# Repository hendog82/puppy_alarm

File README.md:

# Puppy Alarm Clock
Do you hate waking up to your alarm clock? Well, now you can wake up to your puppy licking your face instead. 

This gadget allows you to set a wake up time, and then it will open your dogs crate at the specified time, allowing your dog to jump on your bed and wake you up. 

### Firmware
The firmware is based on the [restful server example](https://github.com/espressif/esp-idf/tree/master/examples/protocols/http_server/restful_server) from the ESP-IDF. The firmware connects to the WiFi network and hosts a local website (so that any device connected to the same network can access it).

Users can connect to this local web page to set the alarm time (using post requests). The ESP gets the current time using NTP, and if the times match the ESP will turn on the motor, opening the dog create. 

### Webpage
The webpage has a live clock and selectable options to set the wake up time, which is then sent to the ESP 32 using a post request. The source code is in the `/front/web-demo/dist` folder.

### Hardware
I generated a simple 2-layer PCB using EAGLE. The files are in the `/board_files` folder. This PCB connects the [ESP-32 huzzah Dev board](https://www.adafruit.com/product/3405) to an H-Bridge that can drive the motor in either direction, and to a button that is used to reset the motor position (or any other desired function. It also has LED's to indicate motor spin direction. The board is powered using 5V from the micro-usb port on the dev board.

#### Pin Assignment:
The following GPIO's of the ESP32 Dev Board are connected

| ESP32  | Function       |
| ------ | -------        |
| GPIO27 | Motor Forwards |
| GPIO33 | Motor Backwards|
| GPIO16 | Button Input   |

### 3D Printed Housing
The STL files for the 3D printed housing are in the `/housing` folder.

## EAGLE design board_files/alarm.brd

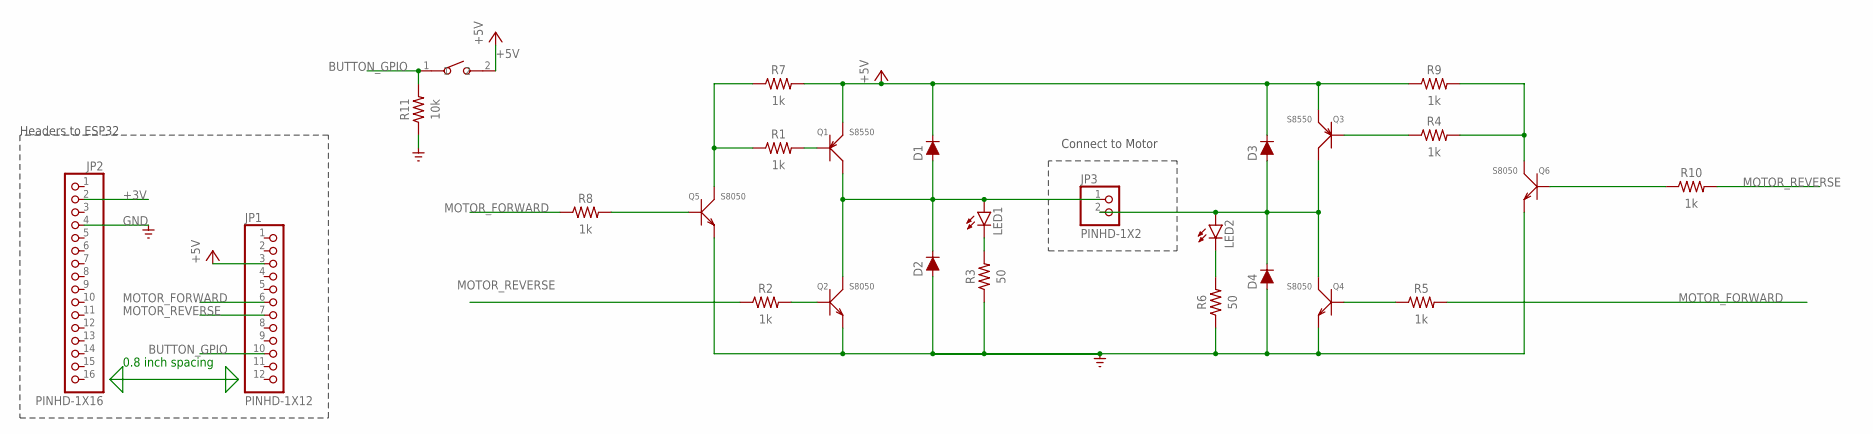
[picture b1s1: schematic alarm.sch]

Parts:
D1, D2, D3, D4: 250mA/100V; SOD-323
JP1: PINHD-1X12; 1X12
JP2: PINHD-1X16; 1X16
JP3: PINHD-1X2; 1X02
LED1: LED-GREEN0603; 0603-GREEN
LED2: LED-ORANGE0603; 0603-ORANGE
Q1, Q3: S8550; SOT-23
Q2, Q4, Q5, Q6: S8050; SOT-23
R1, R2, R4, R5, R7, R8, R9, R10: 1k; RESC1608X60
R3, R6: 50; RESC1608X60
R11: 10k; RESC1608X60
SW1: B3U-1000P-2P-SMD; SW2-2.6-3.0X2.5X1.2+0.4MM

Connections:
+3V: JP2.2
+5V: D1.C, D3.C, JP1.3, Q1.2 (E), Q3.2 (E), R7.2, R9.1, SW1.2
BUTTON_GPIO: JP1.10, R11.2, SW1.1
GND: D2.A, D4.A, JP2.4, Q2.2 (E), Q4.2 (E), Q5.2 (E), Q6.2 (E), R3.1, R6.1, R11.1
MOTOR_BLACK: D3.A, D4.C, JP3.2, LED2.A, Q3.3 (C), Q4.3 (C)
MOTOR_FORWARD: JP1.6, R5.2, R8.1
MOTOR_RED: D1.A, D2.C, JP3.1, LED1.A, Q1.3 (C), Q2.3 (C)
MOTOR_REVERSE: JP1.7, R2.1, R10.2
unnamed: Q1.1 (B), R1.2
unnamed: Q2.1 (B), R2.2
unnamed: LED1.C, R3.2
unnamed: Q5.1 (B), R8.2
unnamed: Q3.1 (B), R4.1
unnamed: Q4.1 (B), R5.1
unnamed: LED2.C, R6.2
unnamed: Q5.3 (C), R1.1, R7.1
unnamed: Q6.3 (C), R4.2, R9.2
unnamed: Q6.1 (B), R10.1

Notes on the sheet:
0.8 inch spacing
Headers to ESP32
Connect to Motor

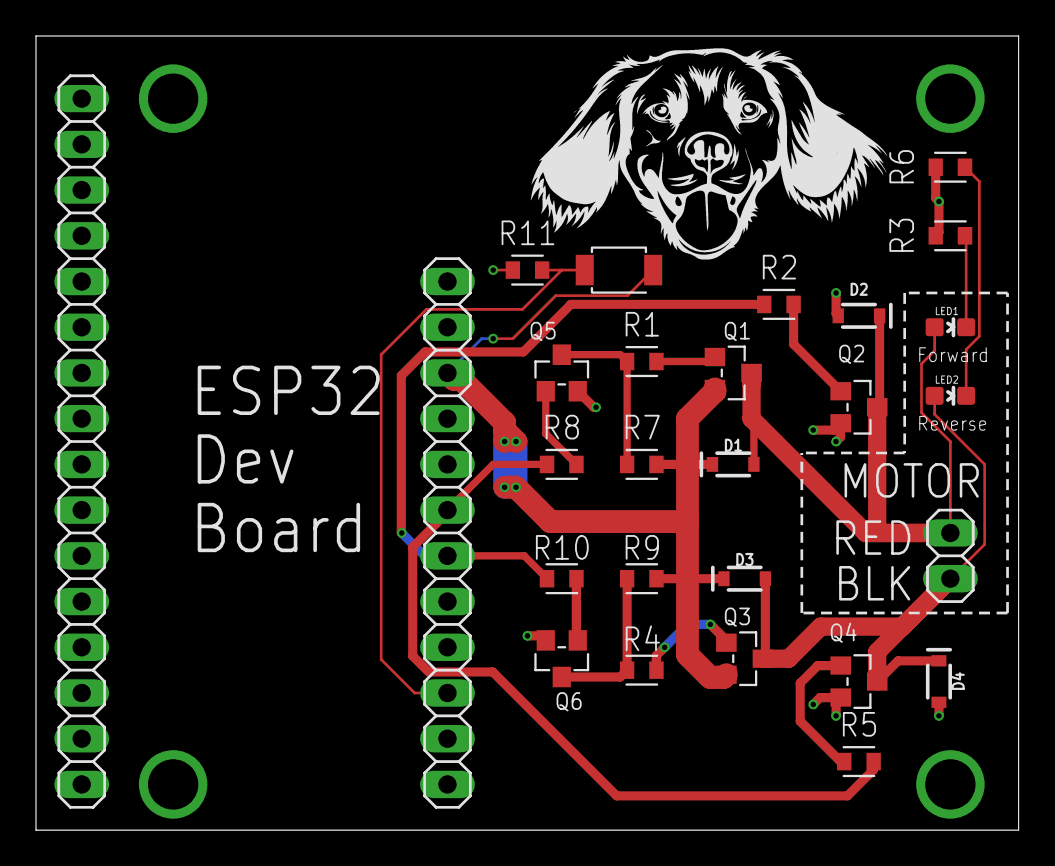
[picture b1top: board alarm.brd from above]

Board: 2 copper layers, 54.6 x 44.1 mm, 27 parts (0 on the bottom side), 17 nets.

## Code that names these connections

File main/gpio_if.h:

#define MOTOR_FORWARD_GPIO		27
#define MOTOR_REVERSE_GPIO		33
#define BUTTON_GPIO				14

#define GPIO_OUTPUT_PIN_SEL  ((1ULL<<MOTOR_FORWARD_GPIO)|(1ULL<<MOTOR_REVERSE_GPIO))
#define GPIO_INPUT_PIN_SEL   (1ULL<<BUTTON_GPIO)


/*
 * Initializes all motor and button functions:
 *
 * 		(1) calls motor_init(), button_init(),
 * 		(2) sets up button isr handler
 * 		(3) starts button task.
 *
 */
void gpio_init();

/*
 * initialize motor gpios
 */
void motor_init();

/*
 * interrupt handler for button
 */
void button_isr_handler(void* arg);

/*
 * task to receive button interrupts.
 */
void Button_Task(void* arg);

/*
 * initialize button gpio
 */
void button_init();

/*
 * spin motor forwards for 3 seconds
 */
void motor_forward();

/*
 * spin motor backwards for 3 seconds
 */
void motor_reverse();

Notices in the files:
parts and their libraries:
SparkFun-DiscreteSemi: Licensing: Creative Commons ShareAlike 4.0 International - https://creativecommons.org/licenses/by-sa/4.0
